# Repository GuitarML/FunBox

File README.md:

# Funbox

Funbox is a digital stereo guitar effect platform using the Daisy Seed by Electrosmith.
This repo includes the KiCad design files for the PCB, as well as software packages to configure your
Funbox as a fully featured guitar pedal. You can build your own and use the effects included here,
or use it as a starting place to design your own awesome pedal!

Video Demos on YouTube:

[Mars Amp Sim/Delay](https://youtu.be/e60Wy_VvJX8?si=AbR1MXqZ35HZ0Mvu), [Jupiter Reverb Shaper](https://youtu.be/iQnR0dN56QY?si=inZRtJW6ivPTOBN7),
[Neptune Reverb/Delay](https://youtu.be/nuLmwTXF1v8?si=5k8mRED5zVJWO6t1), [Pluto Dual Looper](https://youtu.be/xCFR0EeIMSg?si=6pakTC9j9leRP9t6),
[Venus Spectral Reverb](https://youtu.be/IHFEQsWR4W4?si=BbFsI6RXE-6vq7Sy), [Saturn Spectral Delay](https://youtu.be/adQQrBSwXU4?si=lk55HOxCmDiPBn_s),
[MidiKeys Synth](https://youtu.be/qRBMoK8jLx0?si=yauST03D38Y4MzrH), [Mercury Amp Emulator](https://youtu.be/-yD2pLMCNi4?si=rLxFXH2HT4IHW6-g),
[Earth Plate Reverb/Octave](https://youtu.be/5oxMYXyyZHo?si=3_w1OVgaGqCgooyH) [Uranus Granular Delay and Synth](https://youtu.be/lxxZvYDoElI?si=sbfe8fWKY_A6ajux)

Read the [Funbox Build Guide](https://medium.com/@keyth72/funbox-build-guide-afbd8046121e) for a step by step on ordering parts, soldering and assembling the pcb and hardware, and uploading programs to the Funbox.

The resources included here allow you to build a guitar pedal with comparable features to commercial brands. 
Soldering is required to build the hardware. Tayda drill templates are linked along with an Adobe Illustrator 
template for UV printing the enclosure, if desired. 

## Hardware

The Funbox pedal consists of the following main components:

 - Daisy Seed (order from [Electro-Smith](https://www.electro-smith.com/)) - $30
 - Funbox PCB (order from OSHPark or other manufacturer) - $30 for minimum of 3 from OshPark
 - 125B Enclosure ([Powder coat](https://www.taydaelectronics.com/cream-125b-style-aluminum-diecast-enclosure.html), [Custom Drill](https://www.taydaelectronics.com/125b-custom-drill-enclosure-service.html), and [UV print](https://www.taydaelectronics.com/125b-uv-printing-service.html) ordered from [Tayda](https://www.taydaelectronics.com/)) - $15
 - Electronic Components (Tayda, Mouser, Amazon, Digikey (for Dipswitches) etc.)
 - Hardware Components for Funbox (1/4" Stereo Audio Jacks, Power Jack, Knobs, Switches) (I like [LoveMySwitches](https://lovemyswitches.com/))
 - "Funbox" Software - Build your own binary from this repo or download .bin from the [Releases page](https://github.com/GuitarML/FunBox/releases)
<br><br>
There are alot of variables in building your own pedal, but typically the Funbox will cost around $120 to $150 to build.

IMPORTANT: If you use the Drill Template, double check that the hole diameters match your components. Especially for the LED's, which use the larger diameter hole for 5mm [LED Bezel](https://lovemyswitches.com/5mm-chrome-metal-led-bezel-bag-of-5/).

The PCB design KiCad is provided [here](https://github.com/GuitarML/Funbox/blob/main/hardware/funbox_v3_midi_exp), which can be used to order from a manufacturer such as OSHPark or PCBWay.<br>
<br>
Component values are printed on the board for easy assembly! (OSHPark render shown here)

## Software

The following pedal modules are provided here:

Planet Series
- [Mercury](https://github.com/GuitarML/Mercury): An amp emulator running NAM Neural Amp Modeler and a 4 band EQ.
- [Venus](https://github.com/GuitarML/Funbox/blob/main/software/Venus): A Spectral Reverb using a FFT to create shimmery, ethereal soundscapes.
- [Earth](https://github.com/GuitarML/Earth): A Plate Reverb with octave and overdrive effects.
- [Mars](https://github.com/GuitarML/Funbox/blob/main/software/Mars): An amp sim/delay using neural models and Impulse Responses and three delay modes.
- [Jupiter](https://github.com/GuitarML/Funbox/blob/main/software/Jupiter): A Reverb with a focus on EQ for shaping the sound.
- [Saturn](https://github.com/GuitarML/Funbox/blob/main/software/Saturn): A Spectral delay using a FFT to delay different frequencies individually.
- [Uranus](https://github.com/GuitarML/Funbox/blob/main/software/Uranus): A granular delay and FM synth.
- [Neptune](https://github.com/GuitarML/Funbox/blob/main/software/Neptune): A Reverb/Delay capable of ethereal sounds.
- [Pluto](https://github.com/GuitarML/Funbox/blob/main/software/Pluto): A Dual/Stereo looper with variable speed/direction control and real time loop effects.

There are also a couple [Experiments](https://github.com/GuitarML/Funbox/blob/main/software/Experiments) including a Chorus/Reverb and FFT based filter.

Download the compiled modules for the Funbox from the [Releases Page](https://github.com/GuitarML/FunBox/releases).

### Build the Software
Head to the [Electro-Smith Wiki](https://github.com/electro-smith/DaisyWiki) to learn how to set up the Daisy environment on your computer.

```
# Clone the repository
$ git clone https://github.com/GuitarML/Funbox.git
$ cd Funbox

# initialize and set up submodules
$ git submodule update --init --recursive

# Build the daisy libraries (after installing the Daisy Toolchain):
# Replace the daisy_petal files in libDaisy/src with the files in the "mod" directory to properly map controls on Funbox.
$ make -C libDaisy
$ make -C DaisySP

# Build the desired pedal firmware (Mars pedal shown below as example) (after installing the Daisy Toolchain)
$ cd software/Mars
$ make
```

Then upload the firmware (.bin) to your Funbox pedal with the following commands (or use the [Electrosmith Web Programmer](https://electro-smith.github.io/Programmer/))
```
# This is the procedure for uploading to Flash memory on the Daisy Seed, if using SRAM memory use Bootloader method (Mars and Neptune use SRAM).
cd your_pedal
# using USB (after entering bootloader mode)
make program-dfu
# using JTAG/SWD adaptor (like STLink)
make program
```

To upload your firmware to SRAM (more memory available here for larger programs), see the [libdaisy Bootloader Reference](https://electro-smith.github.io/libDaisy/md_doc_2md_2__a7___getting-_started-_daisy-_bootloader.html#autotoc_md49)
or use the [Electrosmith Web Programmer](https://electro-smith.github.io/Programmer/)

To use the Electrosmith Web Programmer to upload programs to SRAM (480KB available instead of 128KB in Flash), do this:
1. Connect to the Daisy Seed as normal from the [Electrosmith Web Programmer](https://electro-smith.github.io/Programmer/).
2. Click "Advanced" button at the bottom, and click "Flash Bootloader Image".
3. On the Daisy Seed, press the RESET button (LED should be lit), and then quickly press the BOOT button. The BOOT LED should now be pulsing.
4. Back in the Web Programmer, choose your .bin file from the "Choose File" button, and then click the "Program" button to upload to SRAM.
5. To load a program back to Flash after using the Bootloader, do the normal upload procedure to overwrite the Bootloader with your new program.

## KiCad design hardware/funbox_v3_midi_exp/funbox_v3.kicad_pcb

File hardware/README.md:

# Hardware

This directory contains the KiCad files for manufacturing the Funbox PCB. Includes schematic, pcb, and generated BOM.
Funbox uses a 125B sized enclosure.

## Funbox v1

VERIFIED WORKING - using OshPark standard board manufacturing

Funbox v1 uses a 125B enclosure with the following features:
- Stereo In/Out
- 9v power
- 6 potentiometer knobs 
- 3 3-way switches On-Off-On
- 2 SPST momentary footswitches
- 2 LEDs
- 2 Dipswitches

[Tayda Drill Template](https://drill.taydakits.com/box-designs/new?public_key=bXVVdnZXK0pOVWJjZG5YOGtwd282Zz09Cg==)

## Funbox v2

Funbox v2 adds MIDI In/Out via two 1/8" TRS jacks and up to a 4 dip switch array, instead of 2.

[Tayda Drill Template](https://drill.taydakits.com/box-designs/new?public_key=M3BDZTdRSmFWRkF4QXpQUzRORjIwQT09Cg==)

CURRENTLY UNTESTED 

## Funbox v3.2

Funbox v3 replaces the MIDI out jack from version 2 with an Expression Input jack. 
Version 3.2 replaces the TL072 Quad Op Amp with a MCP6024 for reduced noise.
Note: Since most Expresion pedals use 1/4" TRS cables, an adapter is required (Female 1/4" to Male 1/8" stereo adapter, or 1/4" to 1/8" TRS cable.)

[Tayda Drill Template](https://drill.taydakits.com/box-designs/new?public_key=M3BDZTdRSmFWRkF4QXpQUzRORjIwQT09Cg==) (Same as version 2)

The Gerber files used for ordering from PCBway have been added in GerberSeed_PCBway_Funbox_v3p2.zip (note that other manufacturers may have different Gerber requirements)

The Funbox v3.2 board is a shared project on OSHPark, click [here](https://oshpark.com/shared_projects/MnthZS4N) to go to the project page for easy ordering.

VERIFIED WORKING

Funbox v3 uses a 125B enclosure with the same features a version 1 with the following additions:
- Midi Input from a 1/8 inch TRS jack
- Expression Input from a 1/8 inch TRS jack
- 4 Dipswitches

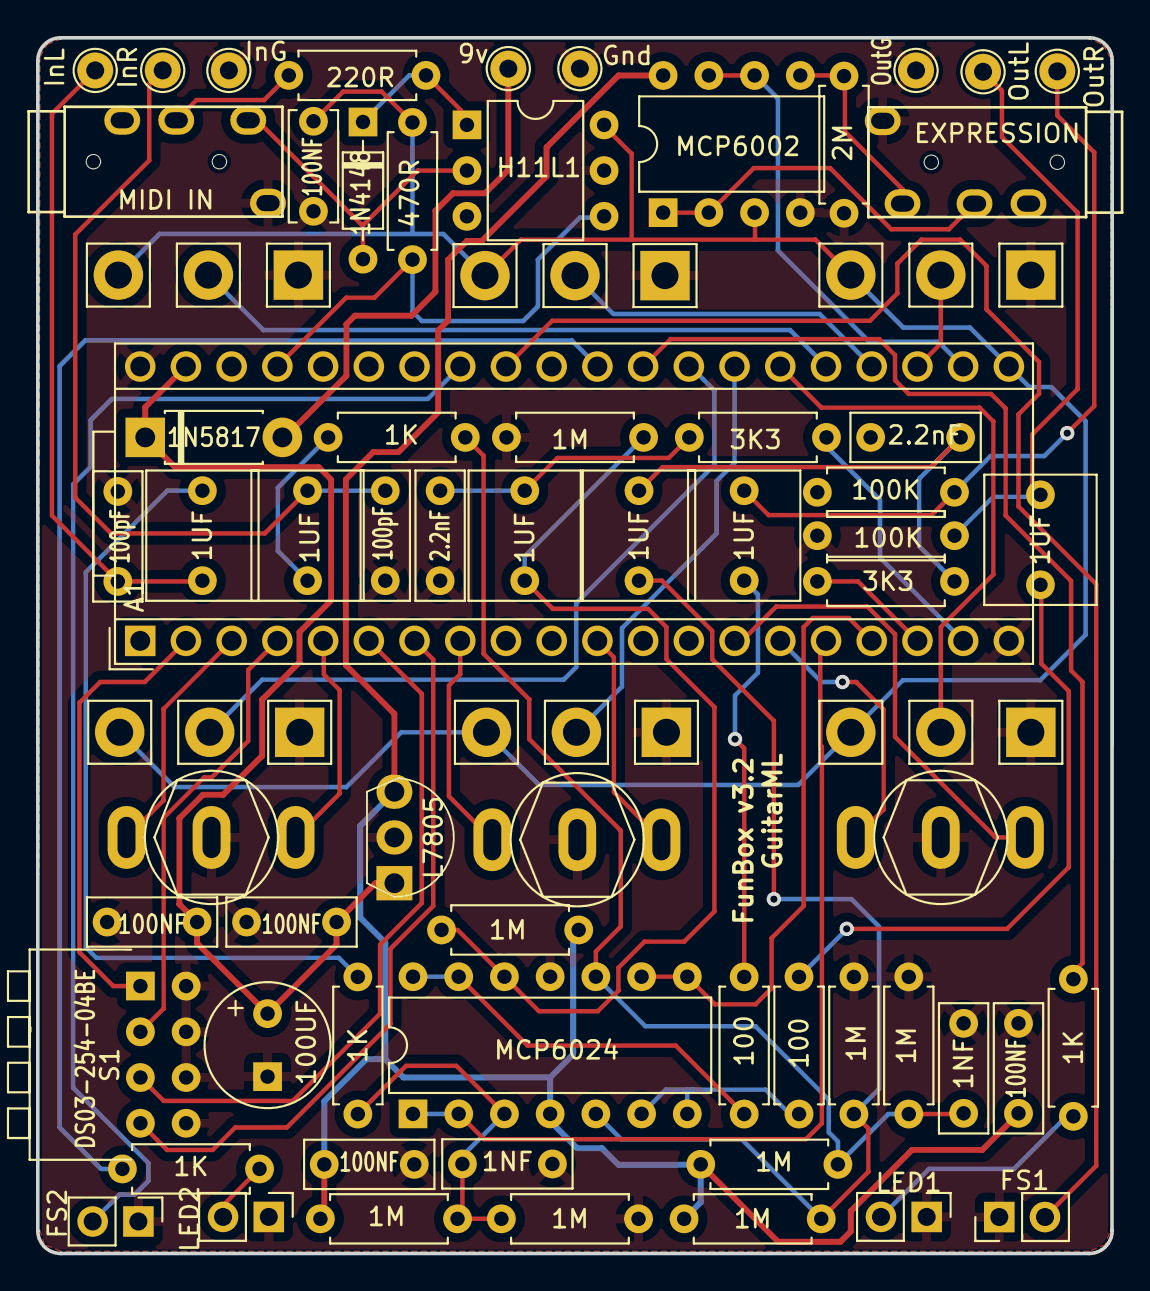
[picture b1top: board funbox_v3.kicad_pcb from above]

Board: 2 copper layers, 59.7 x 67.5 mm, 70 parts (0 on the bottom side), 54 nets.

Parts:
9v: TestPoint_THTPad_D2.0mm_Drill1.0mm
A1: Electrosmith_Daisy_Seed_Rev7; Electrosmith_Daisy_Seed
C1, C4, C5, C14, C15, C17: 1UF; C_Rect_L7.0mm_W6.0mm_P5.00mm
C2, C11: 100pF; C_Rect_L7.0mm_W2.5mm_P5.00mm
C3, C16: 1NF; C_Rect_L7.0mm_W2.5mm_P5.00mm
C6: 100UF; CP_Radial_D8.0mm_P3.50mm
C7, C8, C9, C10: 100NF; C_Rect_L7.0mm_W2.5mm_P5.00mm
C12, C13: 2.2nF; C_Rect_L7.0mm_W2.5mm_P5.00mm
C30: 100NF; C_Disc_D6.0mm_W2.5mm_P5.00mm
D1: 1N5817; D_DO-41_SOD81_P7.62mm_Horizontal
D2: 1N4148; D_DO-35_SOD27_P7.62mm_Horizontal
FS1: Foot_Switch_1; PinHeader_1x02_P2.54mm_Vertical
FS2: Foot_Switch_2; PinHeader_1x02_P2.54mm_Vertical
Gnd: TestPoint_THTPad_D2.0mm_Drill1.0mm
InG: TestPoint_THTPad_D2.0mm_Drill1.0mm
InL: TestPoint_THTPad_D2.0mm_Drill1.0mm
InR: TestPoint_THTPad_D2.0mm_Drill1.0mm
J6: MIDI IN; TRRS-PJ-320A
J7: EXPRESSION; TRRS-PJ-320A
LED1: LED_1; PinHeader_1x02_P2.54mm_Vertical
LED2: LED_2; PinHeader_1x02_P2.54mm_Vertical
OutG: TestPoint_THTPad_D2.0mm_Drill1.0mm
OutL: TestPoint_THTPad_D2.0mm_Drill1.0mm
OutR: TestPoint_THTPad_D2.0mm_Drill1.0mm
POT1, POT2, POT3, POT4, POT5, POT6: 10K; Pot_RightAngle_LongPin_16mm
R1, R2, R5, R6, R13, R14, R15, R16: 1M; R_Axial_DIN0207_L6.3mm_D2.5mm_P7.62mm_Horizontal
R3, R8, R9, R12: 1K; R_Axial_DIN0207_L6.3mm_D2.5mm_P7.62mm_Horizontal
R4, R17: 100; R_Axial_DIN0207_L6.3mm_D2.5mm_P7.62mm_Horizontal
R7, R18: 100K; R_Axial_DIN0207_L6.3mm_D2.5mm_P7.62mm_Horizontal
R10, R11: 3K3; R_Axial_DIN0207_L6.3mm_D2.5mm_P7.62mm_Horizontal
R19: 2M; R_Axial_DIN0207_L6.3mm_D2.5mm_P7.62mm_Horizontal
R30: 220R; R_Axial_DIN0207_L6.3mm_D2.5mm_P7.62mm_Horizontal
R31: 470R; R_Axial_DIN0207_L6.3mm_D2.5mm_P7.62mm_Horizontal
S1: DS03-254-04BE; DS03-254-04BE-dip4
SW1, SW2, SW3: SW_SPDT; SW_Toggle_SPDT_lugs
U1: MCP6024; DIP-14_W7.62mm
U2: L7805; TO-220-3_Vertical
U3: MCP6002; DIP-8_W7.62mm
U5: H11L1; DIP-6_W7.62mm

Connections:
3V3_A: A1.21 (3V3_A), C30.1, POT1.3, POT2.3, POT3.3, POT4.3, POT5.3, POT6.3, R31.1, U3.3 (+), U5.6
5V: C9.2, C10.2, R2.1, R5.1, R13.1, R15.1, U1.4 (V+), U2.3 (OUT), U3.8 (V+)
AUDIO_IN_BUFFER_LEFT: A1.16 (AUDIO_IN_1), U1.1, U1.2 (-)
AUDIO_IN_BUFFER_RIGHT: A1.17 (AUDIO_IN_2), U1.8, U1.9 (-)
AUDIO_OUT_BUFFER_LEFT: A1.18 (AUDIO_OUT_1), R11.1
AUDIO_OUT_BUFFER_RIGHT: A1.19 (AUDIO_OUT_2), R10.1
DIP1: A1.2 (SD_DATA_3), S1.1A
DIP2: A1.4 (SD_DATA_1), S1.2A
DIP3: A1.6 (SD_CMD), S1.3A
DIP4: A1.7 (SD_CLK), S1.4A
EXPRESSION_IN: A1.22 (ADC_0), U3.6 (-), U3.7
EXPRESSION_IN_JACK: J7.T, R19.1, U3.5 (+)
EXPRESSION_REF: J7.R1, U3.1, U3.2 (-)
FOOT_SWITCH_1: A1.32 (SAI2_SD_B), FS1.2
FOOT_SWITCH_2: A1.33 (SAI2_SD_A), FS2.2
GND: A1.20 (AGND), A1.40 (DGND), C2.2, C3.1, C6.1, C7.1, C8.1, C9.1, C10.1, C11.2, C12.2, C13.2, C16.1, C30.2, FS1.1, FS2.1, Gnd.1, InG.1, J6.S, J7.S, LED1.1 (K), LED2.1 (K), OutG.1, POT1.1, POT2.1, POT3.1, POT4.1, POT5.1, POT6.1, R1.2, R6.2, R7.1, R14.2, R16.2, R18.1, R19.2, S1.1B, S1.2B, S1.3B, S1.4B, SW1.2 (B), SW2.2 (B), SW3.2 (B), U1.11 (V-), U2.2 (GND), U3.4 (V-), U5.5
LED_1: A1.29 (DAC_OUT2), R8.2
LED_2: A1.30 (DAC_OUT1), R9.2
MIDI_IN: A1.37 (USB_D_+), R31.2, U5.4
MIDI_IN_JACK_PIN4: J6.R1, R30.1
MIDI_IN_JACK_PIN5: D2.2 (A), J6.T, U5.2
unnamed: 9v.1, D1.2 (A)
unnamed: C1.2, R3.1
unnamed: C5.2, R4.2
unnamed: C4.1, C12.1, R11.2
unnamed: C13.1, C15.1, R10.2
unnamed: C14.2, R12.1
unnamed: C17.2, R17.2
unnamed: D2.1 (K), R30.2, U5.1
unnamed: C1.1, C2.1, InL.1
unnamed: C11.1, C14.1, InR.1
unnamed: LED1.2 (A), R8.1
unnamed: LED2.2 (A), R9.1
unnamed: C5.1, OutL.1, R7.2
unnamed: C17.1, OutR.1, R18.2
unnamed: C3.2, R1.1, R2.2, R3.2, U1.3 (+)
unnamed: C4.2, R5.2, R6.1, U1.5 (+)
unnamed: R4.1, U1.6 (-), U1.7
unnamed: C16.2, R12.2, R15.2, R16.1, U1.10 (+)
unnamed: C15.2, R13.2, R14.1, U1.12 (+)
unnamed: R17.1, U1.13 (-), U1.14
POT_1: A1.23 (ADC_1), POT1.2
POT_2: A1.24 (ADC_2), POT2.2
POT_3: A1.25 (ADC_3), POT3.2
POT_4: A1.26 (ADC_4), POT4.2
POT_5: A1.27 (ADC_5), POT5.2
POT_6: A1.28 (ADC_6), POT6.2
SW1_LEFT: A1.15 (USART1_RX), SW1.3 (C)
SW1_RIGHT: A1.14 (USART1_TX), SW1.1 (A)
SW2_LEFT: A1.8 (SPI1_CS), SW2.3 (C)
SW2_RIGHT: A1.11 (SPI1_PICO), SW2.1 (A)
SW3_LEFT: A1.3 (SD_DATA_2), SW3.3 (C)
SW3_RIGHT: A1.5 (SD_DATA_0), SW3.1 (A)
VCC: A1.39 (VIN), C6.2, C7.2, C8.2, D1.1 (K), U2.1 (IN)

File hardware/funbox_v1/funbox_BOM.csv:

"Source:","/Users/keithbloemer/Desktop/KiCad/FunBox/funbox.kicad_sch"
"Date:","2024 May 01, Wednesday 12:14:24"
"Tool:","Eeschema 7.0.6-0"
"Generator:","/Applications/KiCad/KiCad.app/Contents/SharedSupport/plugins/bom_csv_grouped_by_value.py"
"Component Count:","61"

"Collated Components:"

"Item","Qty","Reference(s)","Value","LibPart","Footprint","Datasheet","DNP","MANUFACTURER","MAXIMUM_PACKAGE_HEIGHT","PARTREV","STANDARD"
"1","8","9v1, Gnd1, In1, In2, InG1, Out1, Out2, OutG1","~","Connector_Generic:Conn_01x01","TestPoint:TestPoint_THTPad_D2.0mm_Drill1.0mm","~","","","","",""
"2","1","A1","Electrosmith_Daisy_Seed_Rev7","MCU_Module:Electrosmith_Daisy_Seed_Rev4","Module:Electrosmith_Daisy_Seed","https://static1.squarespace.com/static/58d03fdc1b10e3bf44256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","","","","",""
"3","6","C1, C4, C5, C14, C15, C17","1UF","Device:C","Capacitor_THT:C_Rect_L7.0mm_W6.0mm_P5.00mm","~","","","","",""
"4","2","C2, C11","100","Device:C","Capacitor_THT:C_Rect_L7.0mm_W2.5mm_P5.00mm","~","","","","",""
"5","2","C3, C16","1NF","Device:C","Capacitor_THT:C_Rect_L7.0mm_W2.5mm_P5.00mm","~","","","","",""
"6","1","C6","100UF","Device:C","Capacitor_THT:CP_Radial_D8.0mm_P3.50mm","~","","","","",""
"7","4","C7, C8, C9, C10","100NF","Device:C","Capacitor_THT:C_Rect_L7.0mm_W2.5mm_P5.00mm","~","","","","",""
"8","2","C12, C13","2.2nF","Device:C","Capacitor_THT:C_Rect_L7.0mm_W2.5mm_P5.00mm","~","","","","",""
"9","1","D1","1N5817","Diode:1N5817","Diode_THT:D_DO-41_SOD81_P7.62mm_Horizontal","http://www.vishay.com/docs/88525/1n5817.pdf","","","","",""
"10","1","FS1","Foot_Switch_1","Switch:SW_Push","Connector_PinHeader_2.54mm:PinHeader_1x02_P2.54mm_Vertical","~","","","","",""
"11","1","FS2","Foot_Switch_2","Switch:SW_Push","Connector_PinHeader_2.54mm:PinHeader_1x02_P2.54mm_Vertical","~","","","","",""
"12","1","LED1","LED_1","Device:LED","Connector_PinHeader_2.54mm:PinHeader_1x02_P2.54mm_Vertical","~","","","","",""
"13","1","LED2","LED_2","Device:LED","Connector_PinHeader_2.54mm:PinHeader_1x02_P2.54mm_Vertical","~","","","","",""
"14","6","POT1, POT2, POT3, POT4, POT5, POT6","10K","Device:R_Potentiometer_US","Potentiometer_THT:Pot_RightAngle_LongPin_16mm","~","","","","",""
"15","8","R1, R2, R5, R6, R13, R14, R15, R16","1M","Device:R","Resistor_THT:R_Axial_DIN0207_L6.3mm_D2.5mm_P7.62mm_Horizontal","~","","","","",""
"16","4","R3, R8, R9, R12","1K","Device:R","Resistor_THT:R_Axial_DIN0207_L6.3mm_D2.5mm_P7.62mm_Horizontal","~","","","","",""
"17","2","R4, R17","100","Device:R","Resistor_THT:R_Axial_DIN0207_L6.3mm_D2.5mm_P7.62mm_Horizontal","~","","","","",""
"18","2","R7, R18","100K","Device:R","Resistor_THT:R_Axial_DIN0207_L6.3mm_D2.5mm_P7.62mm_Horizontal","~","","","","",""
"19","2","R10, R11","3K3","Device:R","Resistor_THT:R_Axial_DIN0207_L6.3mm_D2.5mm_P7.62mm_Horizontal","~","","","","",""
"20","1","S1","DS03-254-02BE","DS03-254-02BE:DS03-254-02BE","Button_Switch_THT:DS03-254-02BE-dip2","","","CUI Inc.","9.93 mm","V1.0","Manufacturer Recommendations"
"21","3","SW1, SW2, SW3","SW_SPDT","Switch:SW_SPDT","Button_Switch_THT:SW_Toggle_SPDT_lugs","~","","","","",""
"22","1","U1","TL074","Amplifier_Operational:TL074","Package_DIP:DIP-14_W7.62mm","http://www.ti.com/lit/ds/symlink/tl071.pdf","","","","",""
"23","1","U2","L7805","Regulator_Linear:L7805","Package_TO_SOT_THT:TO-220-3_Vertical","http://www.st.com/content/ccc/resource/technical/document/da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","","","","",""

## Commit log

2024-05-01 Added kicad files
2024-05-02 Module updates and added draft mars effect
2024-05-03 Mars compiles
2024-05-03 Neptune compiles
2024-05-03 Fixed makefile
2024-05-17 Added chorusverb, fixes to mars and neptune
2024-05-17 Added funbox v2 and v3 kicad files
2024-05-18 Updated mars
2024-05-18 mars updates
2024-05-18 Updated neptune
2024-05-18 Updated neptune reverb params
2024-05-19 Adjusted levels for mars
2024-05-20 Updated Mars to use Eigen from RTNeural
2024-05-20 Updated graphics, added readmes
2024-05-20 Added template.cpp, updated Readmes
2024-05-20 Updated delay code
2024-05-21 Added License
2024-05-21 Added images and updated readmes
2024-05-21 Added drill template link
2024-05-21 Added drill template links
2024-05-21 Updated references
2024-05-21 Upated neptune readme
2024-05-21 Updated mars dipswitch operation
2024-05-21 Updates to neptune
2024-05-21 Added infographics
2024-05-22 Updated for version 3 pcb
2024-05-24 Added expressionHandler.h for expression pedal operation
2024-05-24 Added midi support
2024-05-29 Added Jupiter
2024-05-29 Added Pluto draft
2024-05-30 Updates and fixes to Jupiter and Pluto
2024-05-30 Added reverb and filter effects to Pluto
2024-05-31 Updates to Pluto
2024-05-31 Updated readmes
2024-05-31 Updated RTNeural to older commit for compatibility
2024-05-31 Updated Neptune decay range and readmes
2024-06-08 Updated mars IRs, effects order
2024-06-08 Rewrote Jupiter with a focus on EQ
2024-06-08 Tweaked Jupiter params
2024-06-08 Updated readme to match new controls
2024-06-09 Updated stability to use smoothrandom
2024-06-09 Readme updates
2024-06-09 Updated stepped mode to do 5ths and octaves
2024-06-09 Updated filter
2024-06-12 Added expression handling to Mars, updated infographics
2024-06-12 Added FFT experiment, updated template
2024-06-13 Removed unused code
2024-06-15 Updated to version 3.1, fix expression, adjusted pieces
2024-06-15 Updated images and readme for v3 hardware
2024-06-15 Added bksheperd framework definitions
2024-06-16 Image and readme updates
2024-06-17 Updated version2 pcb. Updated expression for Jupiter, Neptune, and Pluto
2024-06-17 Fixed looper led logic when switching out of Set Expression mode
2024-06-18 Initial midi control added to Pluto
2024-06-19 Added initial preset action using qpsi for footswitch 2
2024-06-19 Syncing branch
2024-06-19 Added blink for indicating saving a preset
2024-06-20 Updated to run in flash, updated footswitch logic
2024-06-20 Added preset to Jupiter, Neptune, updated Mars. Updated infographics and readmes.
2024-06-21 Fixed jupiter params logic
2024-06-21 Fixed neptune switch logic
2024-06-21 Fixed neptune switches on start up
2024-06-22 Updated readme with software descriptions
2024-06-22 Updated images
2024-06-22 Added link
2024-06-22 Fixed spacing
2024-06-22 Updated readme with releases page
2024-06-22 Removed WIP statement
2024-06-22 Added download count icon
2024-06-24 Fixed Pluto LED blink, updated neptune reverb mode, updated infographics
2024-06-24 Fixed bug in switch logic
2024-06-24 Updated build instructions
2024-06-24 Added pF label for clarity
2024-06-25 Added MidiKeys experiment
2024-06-25 Fixed midi for Jupiter
2024-06-25 Updated Jupiter readme and infographic
2024-06-25 Updated midikeys with synth and delay effect
2024-06-26 Added midi knob control to Neptune
2024-06-26 Updated neptune info
2024-06-29 Added gerber files, updated readme
2024-06-29 Added expression control to knob 1
2024-06-29 Updated range for damping control
2024-06-29 Added dotted 8th delay
2024-07-13 Updated board to v3.2 to use MCP6024 op amp instead of TL074
2024-07-13 Updated render to v3.2
2024-07-22 Updated readme with demo links
2024-07-24 Added spectral reverb experiment
2024-07-24 Added shimmer modes
2024-07-29 Added Venus
2024-07-29 Updated main readme with Venus link
2024-08-11 Added Saturn module
2024-08-12 Added NoiseFilterFFT experiment
2024-10-29 Updated bom units
2024-11-01 Fixed Bom
2024-11-07 Added info to BOM
2025-01-10 Staged dependencies and documentation for new modules
2025-01-10 Added earth and mercury as submodules
2025-01-10 Added infographics for earth and mercury
2025-01-12 Update readme links
2025-01-16 Added mercury demo link
2025-01-22 Added initial fm synth experiment
2025-01-22 Fixed ifelse typo
2025-01-22 Parameter adjustments
2025-01-25 Added granularplayer test
2025-01-30 Updated granular experiment, fixed audio sample fading
2025-02-12 Added Uranus Module
2025-02-12 Code cleanup, readme updates, infographic updates
2025-02-25 Updated readme and v3 bom
2026-04-12 initial pluto tweaks
    reduce block size to 1, 48k sample rate. 48k reverb, and MIDI expression control adjustment.
2026-04-28 add first dwarf planet
2026-04-28 three modes implemented.
2026-04-29 initial control tweaks
2026-04-29 add expression control for envelope follower
2026-05-02 v1 - core features
2026-06-27 Ported Balnea to funbox
2026-06-27 Fixing infographics conflict
2026-06-27 Updated infographics for balnea
2026-06-27 Revert "Updated infographics for balnea"
    This reverts commit 9d9904b8d6e6f0ca6fffe39f09e870210c56e392.
2026-06-27 Updated balnea tap led
